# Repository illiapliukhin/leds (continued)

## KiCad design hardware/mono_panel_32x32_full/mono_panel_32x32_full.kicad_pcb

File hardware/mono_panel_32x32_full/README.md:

# mono_panel_32x32_full — edge-to-edge 32×32 panel for seamless tiling

A drop-in alternative to `mono_panel_32x32`: same two Hirose `FH12-40S-0.5SH` receptacles, same pinout and LED net mapping
(`Dn`, n = 32(r−1)+c; LED pad 2 = `ROW_rr_ANODE`, pad 1 = `COL_cc`), Type B FFC pin 1 → pin 1. There is no frame. LEDs fill the
whole front, so butted panels (6-stack, 3×2, 6×1) keep one continuous pixel grid.

## Geometry (for the stacking sim)

| | |
|---|---|
| Outline | **160.0 × 160.0 mm**, square, sharp corners, origin at the top-left corner of the front (KiCad +x right, +y down) |
| Pitch | **5.0 mm** in x and y |
| LED centres | x = 2.5 + 5.0·(c−1), y = 2.5 + 5.0·(r−1); the outermost LED centre is **2.5 mm (pitch/2)** from every edge |
| Across a seam | centre-to-centre = 5.0 mm, so the pitch is continuous; 3×2 = 480 × 320 mm, 96 × 64 LEDs; 6×1 = 960 × 160 mm |
| LED | NCD0603W1 (0603), long axis vertical, centred on the node; anode north |
| Thickness | 1.6 mm FR4, 4 layers; height with FFC ≈ 1.6 + 2.0 (FH12) mm; SMT standoffs on the back |
| Back parts | J_ROW centre (72.75, 80.0), J_COL centre (107.75, 80.0), both B.Cu, pin 1 at the left (front view), cable exits +y (south). U_ID (91.0, 76.9), C_ID (91.0, 74.3). Standoffs MH1–4 at (20, 16.9), (140, 16.9), (20, 141.9), (140, 141.9) |

## Choices

- **Pitch 5.0 mm (160 mm board).** Recommended over 4.0 and 3.0. 5.0 keeps the 0603 LEDs (good side visibility, the same LED and
  10 mA as today, so brightness per pixel is unchanged) and leaves a 1.7 mm-tall via band and about 4 mm channels per cell. That room is
  what lets the 64 FFC lines fan in on the back without blind vias. 4.0 mm (128 mm) also fits 0603 but the channels hold only about
  5 lines, so the fan-out would need 6 layers or HDI. 3.0 mm (96 mm) needs 0402 and laser vias. Cost per panel is about the same at
  5.0 and 4.0 (the LED count is fixed and the PCB is about 25 % smaller). At 3.0 HDI dominates. The pitch is close to the old
  panel's 5.2 mm, so content scales almost 1:1.
- **4 layers (JLC 1.6 mm, order 1 oz inner copper).** F.Cu: LEDs, 1.0 mm row bus on the anode line, cathode stubs to one
  0.2/0.45 mm via per LED (1.9 mm below the LED centre, so the bottom row's via keeps 0.35 mm to the edge). In1.Cu: the 32 column lines, straight under
  the vias. In2.Cu + B.Cu: FFC fan-out. Rows go straight up/down on B.Cu in the via channels (8 per channel) to a via on their
  own bus. Columns, ID and GND are maze-routed (`route_full.py`, A* on 0.125 mm grid, real clearance ≥ 0.10 mm).
- **Mounting: SMT M2 standoffs on the back, no front holes.** Four Ø4.2 mm SMD pads on B.Cu between via rows. Suggested parts:
  Würth WA-SMSI/WA-SMSN M2 (blind, flat-bottom) or similar no-hole SMT nuts. Check the exact MPN pad before ordering. PEM SMTSO and the
  LCSC SMTSO clones need a Ø3.7 board hole and are **not** compatible. Hand-solder them or consign them to JLC. The front stays solid LEDs.
- **LED interface standard v1** (`hardware/common/LED_INTERFACE_STANDARD.md`): J_ROW 33/38/40 = GND, 39 (`ID_PRESENT_N`) = GND,
  35/36 = ID_SDA/ID_SCL, 37 = ID_3V3; J_COL 33/38/40 = GND; 34 (and J_COL 34–37, 39) are NC. `U_ID` 24LC02BT-I/OT (0x50,
  pin 4 VCC, pin 5 WP = GND, no pull-ups) and `C_ID` 100 nF on ID_3V3. EEPROM record: class = full-bleed, pitch 5.0 mm,
  `row_path_mohm` = 148 (worst row, panel only), mapping identity.

## Current / IR drop (row = 32 × 10 mA = 0.32 A, `analyze_full.py` → `analysis.json`)

| | |
|---|---|
| Row feed | 0.30 mm × 1 oz on B.Cu, ≤ 80.7 mm (ROW_01) = 132 mΩ; jog sections 0.2 mm |
| Row bus | 1.0 mm × 1 oz F.Cu, fed at one point, worst bus drop 4.6 mV |
| Via | 1.75 mΩ (0.2 mm drill, 1.6 mm) |
| **Worst panel drop** | **47 mV at 20 °C, 55 mV at 60 °C** (target ≤ 100 mV) |
| Temperature rise | 0.3 mm at 0.32 A ≈ 4.6 °C (IPC-2221 external, conservative versus IPC-2152) |

## DRC / fab

- `kicad-cli pcb drc --severity-all`: **0 violations, 0 unconnected** (clearance 0.10, track ≥ 0.15, via 0.2/0.45, copper–edge 0.2).
- `./make_fab.sh` → `mono_panel_32x32_full_fab.zip` (Gerbers F/In1/In2/B, drill, BOM + CPL JLC format).
- **Assembly:** LEDs on top (1024 × C84265). The back has 2 × FH12 (C202114), U_ID (C2655410) and C_ID (C1525), so JLC needs **double-sided assembly**.
  A cheaper option: top-side assembly only, then hand-solder the 2 FFCs + 0402 + SOT-23 (and the standoffs).
- **Price (ESTIMATE, JLC/LCSC list prices, `fab/price_estimate.json`, priced BOM `fab/BOM_mono_panel_32x32_full_priced.csv`):**
  parts ≈ $8.5/board (1024 LEDs ≈ $7.0, 2 × FH12 ≈ $1.24, EEPROM $0.27); 4L 160×160 PCB with 1 oz inner ≈ $70 for 5;
  double-sided SMT setup ≈ $50 + 4 extended-part fees ≈ $12 → **≈ $38 per assembled panel at qty 5, ≈ $23 at qty 30**.
  Top-only assembly with the back parts hand-soldered saves about $25 per order.

## Renders (`renders/`)

`full_front_lit.png` (front, lit), `full_back.png` (back: copper of all layers + parts), `full_kicad_top.png` /
`full_kicad_bottom.png` (KiCad 3D), `full_tiled_3x2.png` (3×2 butted wall, red ticks = seams), `full_seam_closeup.png`, `full_sim_bg.png`.

## Regenerate

```
source ../tools/kicad10_env.sh
python3.11 gen_full.py          # base board + fixed.json
python3 route_full.py           # numpy/scipy maze router -> routes.json (~3 min)
python3.11 gen_full.py routes   # final .kicad_pcb
kicad-cli pcb drc --severity-all --format json -o drc.json mono_panel_32x32_full.kicad_pcb
python3 analyze_full.py && python3 render_full.py && ./make_fab.sh
```
Bring-up sim: `firmware/mono_split/sim/bringup/bringup.py --panel full`.

## Bring-up sim (`--panel full`)

`cable.py --panel full`: Type B gives J_ROW1→J_ROW and J_COL1→J_COL pin 1→1 with 0 net mismatches (Type A mirrors 1→40, 32 errors).
Nominal tests: I2C scan, all on, row walk, column walk, and checkerboard all **PASS** (32/32 rows and columns, 0 LED mismatches). Fault injection: F1 (Type A cable) and F2 (open COL_07) are **caught**.
See `firmware/mono_split/sim/bringup/bench_report_full.md` and `png/bringup_full_*.png`.

## LED Vf bin (order note)

NCD0603W1 (C84265) is sold unbinned on LCSC/JLC (2.6–3.6 V @ 5 mA). The main board's 4.24 V rail allows ≤ 3.38 V at 10 mA, which is about ≤ 3.2 V @ 5 mA. **Order Vf bin 2.8–3.0 V @ 5 mA (preferred) or 3.0–3.2 V; reject > 3.2 V**, one bin per panel. The bin is printed as `VF(V)` on the reel label, and NationStar has no part-number suffix for it. With JLC either consign labelled reels or accept unbinned parts and screen at bring-up. Details: `hardware/common/LED_INTERFACE_STANDARD.md` §5.1.

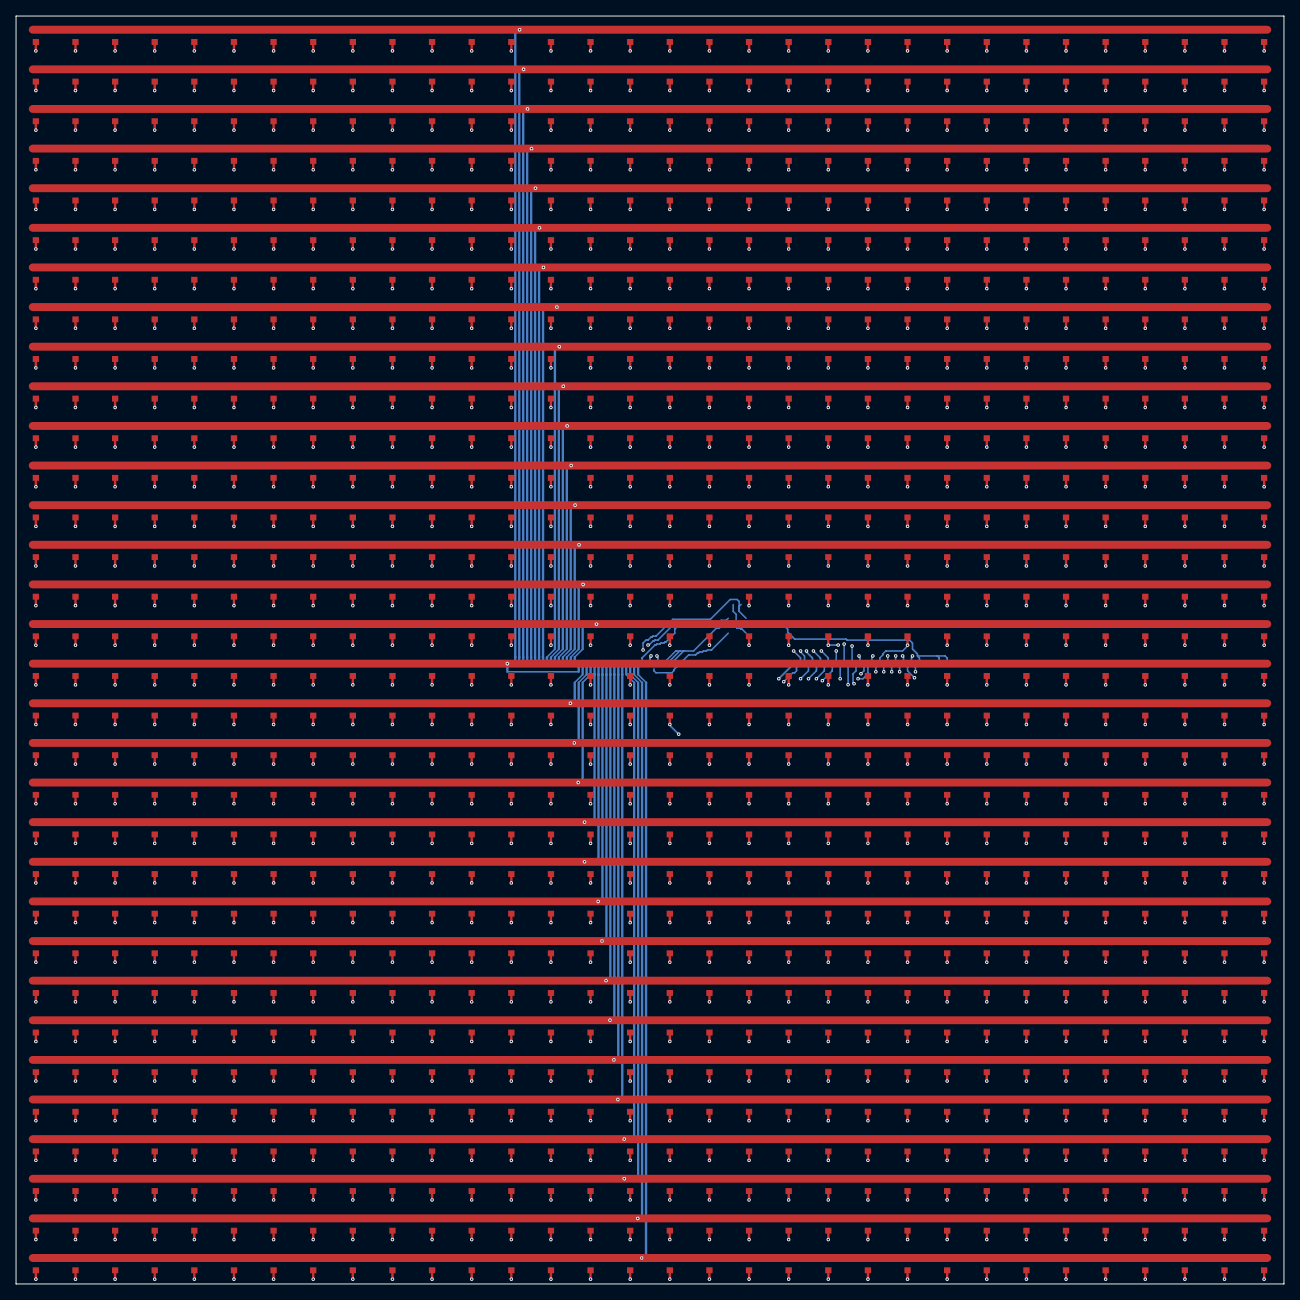
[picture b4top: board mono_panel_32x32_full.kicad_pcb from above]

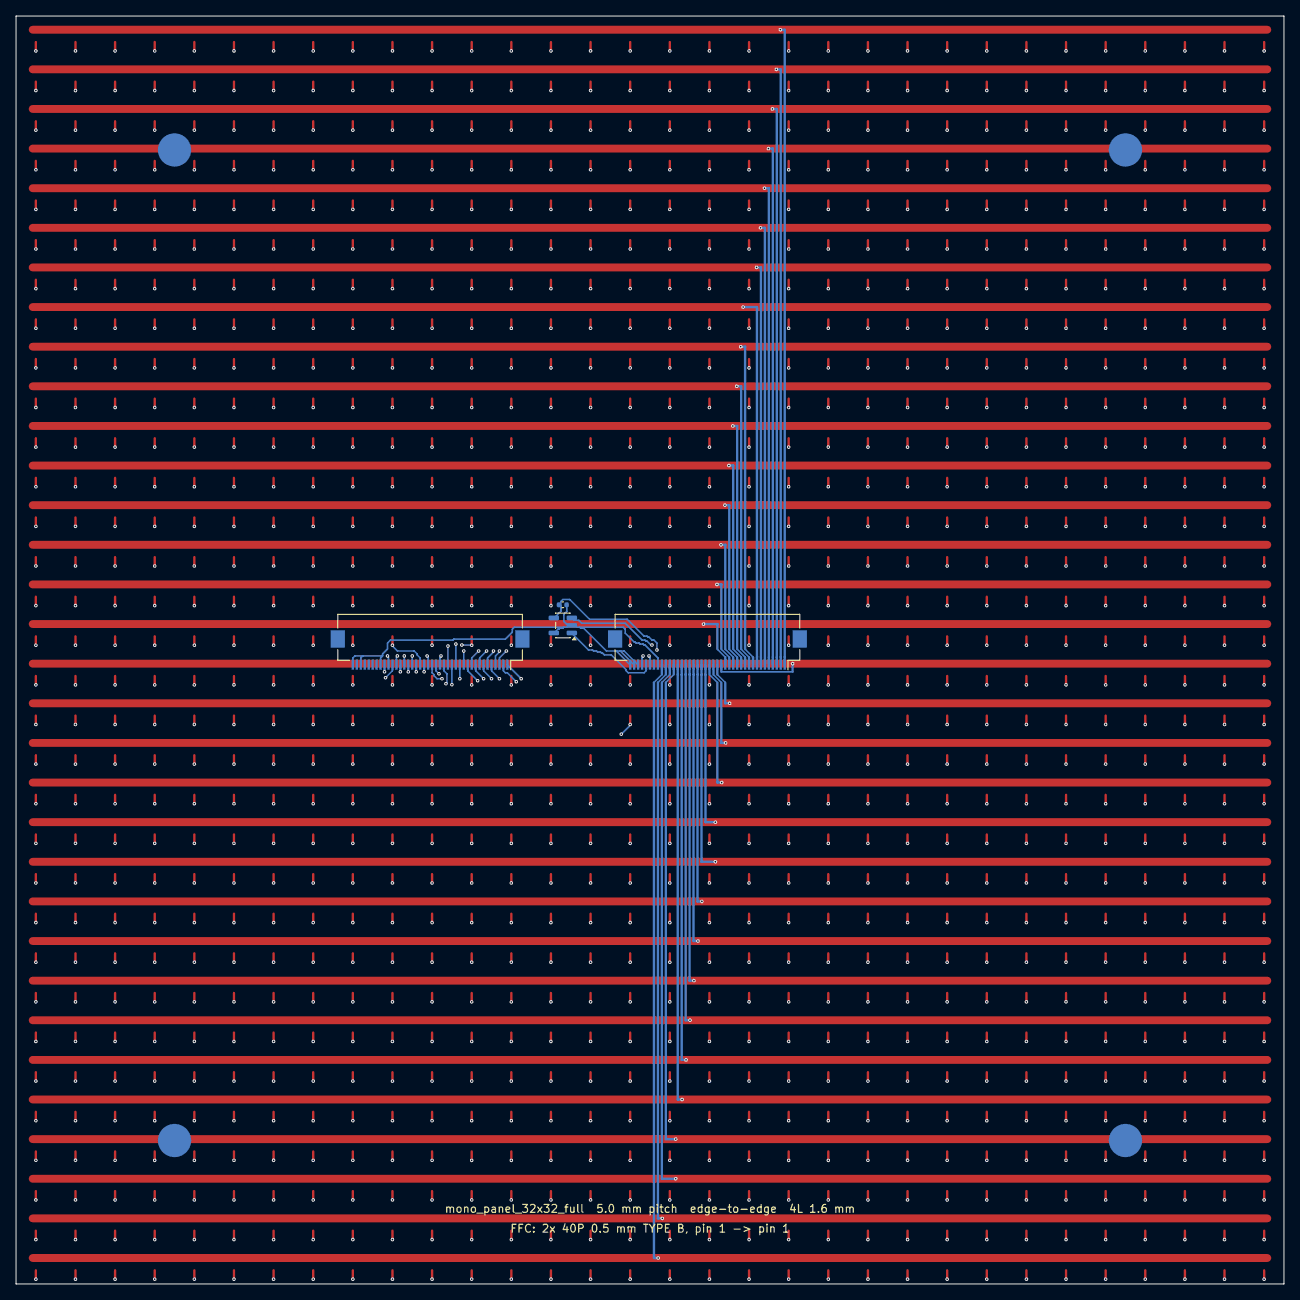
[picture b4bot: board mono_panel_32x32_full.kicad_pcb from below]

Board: 4 copper layers, 160.0 x 160.0 mm, 1032 parts (8 on the bottom side), 68 nets.

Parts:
C_ID: 100n; C_0402_1005Metric
D1, D2, D3, D4, D5, D6, D7, D8, D9, D10, D11, D12, D13, D14, D15, D16, D17, D18, D19, D20, D21, D22, D23, D24, D25, D26, D27, D28, D29, D30, D31, D32, D33, D34, D35, D36, D37, D38, D39, D40, D41, D42, D43, D44, D45, D46, D47, D48, D49, D50, D51, D52, D53, D54, D55, D56, D57, D58, D59, D60, D61, D62, D63, D64, D65, D66, D67, D68, D69, D70, D71, D72, D73, D74, D75, D76, D77, D78, D79, D80, D81, D82, D83, D84, D85, D86, D87, D88, D89, D90, D91, D92, D93, D94, D95, D96, D97, D98, D99, D100, D101, D102, D103, D104, D105, D106, D107, D108, D109, D110, D111, D112, D113, D114, D115, D116, D117, D118, D119, D120, D121, D122, D123, D124, D125, D126, D127, D128, D129, D130, D131, D132, D133, D134, D135, D136, D137, D138, D139, D140, D141, D142, D143, D144, D145, D146, D147, D148, D149, D150, D151, D152, D153, D154, D155, D156, D157, D158, D159, D160, D161, D162, D163, D164, D165, D166, D167, D168, D169, D170, D171, D172, D173, D174, D175, D176, D177, D178, D179, D180, D181, D182, D183, D184, D185, D186, D187, D188, D189, D190, D191, D192, D193, D194, D195, D196, D197, D198, D199, D200, D201, D202, D203, D204, D205, D206, D207, D208, D209, D210, D211, D212, D213, D214, D215, D216, D217, D218, D219, D220, D221, D222, D223, D224, D225, D226, D227, D228, D229, D230, D231, D232, D233, D234, D235, D236, D237, D238, D239, D240, D241, D242, D243, D244, D245, D246, D247, D248, D249, D250, D251, D252, D253, D254, D255, D256, D257, D258, D259, D260, D261, D262, D263, D264, D265, D266, D267, D268, D269, D270, D271, D272, D273, D274, D275, D276, D277, D278, D279, D280, D281, D282, D283, D284, D285, D286, D287, D288, D289, D290, D291, D292, D293, D294, D295, D296, D297, D298, D299, D300, D301, D302, D303, D304, D305, D306, D307, D308, D309, D310, D311, D312, D313, D314, D315, D316, D317, D318, D319, D320, D321, D322, D323, D324, D325, D326, D327, D328, D329, D330, D331, D332, D333, D334, D335, D336, D337, D338, D339, D340, D341, D342, D343, D344, D345, D346, D347, D348, D349, D350, D351, D352, D353, D354, D355, D356, D357, D358, D359, D360, D361, D362, D363, D364, D365, D366, D367, D368, D369, D370, D371, D372, D373, D374, D375, D376, D377, D378, D379, D380, D381, D382, D383, D384, D385, D386, D387, D388, D389, D390, D391, D392, D393, D394, D395, D396, D397, D398, D399, D400, D401, D402, D403, D404, D405, D406, D407, D408, D409, D410, D411, D412, D413, D414, D415, D416, D417, D418, D419, D420, D421, D422, D423, D424, D425, D426, D427, D428, D429, D430, D431, D432, D433, D434, D435, D436, D437, D438, D439, D440, D441, D442, D443, D444, D445, D446, D447, D448, D449, D450, D451, D452, D453, D454, D455, D456, D457, D458, D459, D460, D461, D462, D463, D464, D465, D466, D467, D468, D469, D470, D471, D472, D473, D474, D475, D476, D477, D478, D479, D480, D481, D482, D483, D484, D485, D486, D487, D488, D489, D490, D491, D492, D493, D494, D495, D496, D497, D498, D499, D500, D501, D502, D503, D504, D505, D506, D507, D508, D509, D510, D511, D512, D513, D514, D515, D516, D517, D518, D519, D520, D521, D522, D523, D524, D525, D526, D527, D528, D529, D530, D531, D532, D533, D534, D535, D536, D537, D538, D539, D540, D541, D542, D543, D544, D545, D546, D547, D548, D549, D550, D551, D552, D553, D554, D555, D556, D557, D558, D559, D560, D561, D562, D563, D564, D565, D566, D567, D568, D569, D570, D571, D572, D573, D574, D575, D576, D577, D578, D579, D580, D581, D582, D583, D584, D585, D586, D587, D588, D589, D590, D591, D592, D593, D594, D595, D596, D597, D598, D599, D600, D601, D602, D603, D604, D605, D606, D607, D608, D609, D610, D611, D612, D613, D614, D615, D616, D617, D618, D619, D620, D621, D622, D623, D624, D625, D626, D627, D628, D629, D630, D631, D632, D633, D634, D635, D636, D637, D638, D639, D640, D641, D642, D643, D644, D645, D646, D647, D648, D649, D650, D651, D652, D653, D654, D655, D656, D657, D658, D659, D660, D661, D662, D663, D664, D665, D666, D667, D668, D669, D670, D671, D672, D673, D674, D675, D676, D677, D678, D679, D680, D681, D682, D683, D684, D685, D686, D687, D688, D689, D690, D691, D692, D693, D694, D695, D696, D697, D698, D699, D700, D701, D702, D703, D704, D705, D706, D707, D708, D709, D710, D711, D712, D713, D714, D715, D716, D717, D718, D719, D720, D721, D722, D723, D724, D725, D726, D727, D728, D729, D730, D731, D732, D733, D734, D735, D736, D737, D738, D739, D740, D741, D742, D743, D744, D745, D746, D747, D748, D749, D750, D751, D752, D753, D754, D755, D756, D757, D758, D759, D760, D761, D762, D763, D764, D765, D766, D767, D768, D769, D770, D771, D772, D773, D774, D775, D776, D777, D778, D779, D780, D781, D782, D783, D784, D785, D786, D787, D788, D789, D790, D791, D792, D793, D794, D795, D796, D797, D798, D799, D800, D801, D802, D803, D804, D805, D806, D807, D808, D809, D810, D811, D812, D813, D814, D815, D816, D817, D818, D819, D820, D821, D822, D823, D824, D825, D826, D827, D828, D829, D830, D831, D832, D833, D834, D835, D836, D837, D838, D839, D840, D841, D842, D843, D844, D845, D846, D847, D848, D849, D850, D851, D852, D853, D854, D855, D856, D857, D858, D859, D860, D861, D862, D863, D864, D865, D866, D867, D868, D869, D870, D871, D872, D873, D874, D875, D876, D877, D878, D879, D880, D881, D882, D883, D884, D885, D886, D887, D888, D889, D890, D891, D892, D893, D894, D895, D896, D897, D898, D899, D900, D901, D902, D903, D904, D905, D906, D907, D908, D909, D910, D911, D912, D913, D914, D915, D916, D917, D918, D919, D920, D921, D922, D923, D924, D925, D926, D927, D928, D929, D930, D931, D932, D933, D934, D935, D936, D937, D938, D939, D940, D941, D942, D943, D944, D945, D946, D947, D948, D949, D950, D951, D952, D953, D954, D955, D956, D957, D958, D959, D960, D961, D962, D963, D964, D965, D966, D967, D968, D969, D970, D971, D972, D973, D974, D975, D976, D977, D978, D979, D980, D981, D982, D983, D984, D985, D986, D987, D988, D989, D990, D991, D992, D993, D994, D995, D996, D997, D998, D999, D1000, D1001, D1002, D1003, D1004, D1005, D1006, D1007, D1008, D1009, D1010, D1011, D1012, D1013, D1014, D1015, D1016, D1017, D1018, D1019, D1020, D1021, D1022, D1023, D1024: NCD0603W1
J_COL: FFC_40P_050_COL
J_ROW: FFC_40P_050_ROW
MH1, MH2, MH3, MH4: SMT_STANDOFF_M2; SMT_Standoff_M2_D4.2
U_ID: 24LC02BT-I/OT; SOT-23-5

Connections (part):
COL_01: D1.1 (K), D33.1 (K), D65.1 (K), D97.1 (K), D129.1 (K), D161.1 (K), D193.1 (K), D225.1 (K), D257.1 (K), D289.1 (K), D321.1 (K), D353.1 (K), D385.1 (K), D417.1 (K), D449.1 (K), D481.1 (K), D513.1 (K), D545.1 (K), D577.1 (K), D609.1 (K), D641.1 (K), D673.1 (K), D705.1 (K), D737.1 (K), D769.1 (K), D801.1 (K), D833.1 (K), D865.1 (K), D897.1 (K), D929.1 (K), D961.1 (K), D993.1 (K), J_COL.1
COL_02: D2.1 (K), D34.1 (K), D66.1 (K), D98.1 (K), D130.1 (K), D162.1 (K), D194.1 (K), D226.1 (K), D258.1 (K), D290.1 (K), D322.1 (K), D354.1 (K), D386.1 (K), D418.1 (K), D450.1 (K), D482.1 (K), D514.1 (K), D546.1 (K), D578.1 (K), D610.1 (K), D642.1 (K), D674.1 (K), D706.1 (K), D738.1 (K), D770.1 (K), D802.1 (K), D834.1 (K), D866.1 (K), D898.1 (K), D930.1 (K), D962.1 (K), D994.1 (K), J_COL.2
COL_03: D3.1 (K), D35.1 (K), D67.1 (K), D99.1 (K), D131.1 (K), D163.1 (K), D195.1 (K), D227.1 (K), D259.1 (K), D291.1 (K), D323.1 (K), D355.1 (K), D387.1 (K), D419.1 (K), D451.1 (K), D483.1 (K), D515.1 (K), D547.1 (K), D579.1 (K), D611.1 (K), D643.1 (K), D675.1 (K), D707.1 (K), D739.1 (K), D771.1 (K), D803.1 (K), D835.1 (K), D867.1 (K), D899.1 (K), D931.1 (K), D963.1 (K), D995.1 (K), J_COL.3
COL_04: D4.1 (K), D36.1 (K), D68.1 (K), D100.1 (K), D132.1 (K), D164.1 (K), D196.1 (K), D228.1 (K), D260.1 (K), D292.1 (K), D324.1 (K), D356.1 (K), D388.1 (K), D420.1 (K), D452.1 (K), D484.1 (K), D516.1 (K), D548.1 (K), D580.1 (K), D612.1 (K), D644.1 (K), D676.1 (K), D708.1 (K), D740.1 (K), D772.1 (K), D804.1 (K), D836.1 (K), D868.1 (K), D900.1 (K), D932.1 (K), D964.1 (K), D996.1 (K), J_COL.4
COL_05: D5.1 (K), D37.1 (K), D69.1 (K), D101.1 (K), D133.1 (K), D165.1 (K), D197.1 (K), D229.1 (K), D261.1 (K), D293.1 (K), D325.1 (K), D357.1 (K), D389.1 (K), D421.1 (K), D453.1 (K), D485.1 (K), D517.1 (K), D549.1 (K), D581.1 (K), D613.1 (K), D645.1 (K), D677.1 (K), D709.1 (K), D741.1 (K), D773.1 (K), D805.1 (K), D837.1 (K), D869.1 (K), D901.1 (K), D933.1 (K), D965.1 (K), D997.1 (K), J_COL.5
COL_06: D6.1 (K), D38.1 (K), D70.1 (K), D102.1 (K), D134.1 (K), D166.1 (K), D198.1 (K), D230.1 (K), D262.1 (K), D294.1 (K), D326.1 (K), D358.1 (K), D390.1 (K), D422.1 (K), D454.1 (K), D486.1 (K), D518.1 (K), D550.1 (K), D582.1 (K), D614.1 (K), D646.1 (K), D678.1 (K), D710.1 (K), D742.1 (K), D774.1 (K), D806.1 (K), D838.1 (K), D870.1 (K), D902.1 (K), D934.1 (K), D966.1 (K), D998.1 (K), J_COL.6
COL_07: D7.1 (K), D39.1 (K), D71.1 (K), D103.1 (K), D135.1 (K), D167.1 (K), D199.1 (K), D231.1 (K), D263.1 (K), D295.1 (K), D327.1 (K), D359.1 (K), D391.1 (K), D423.1 (K), D455.1 (K), D487.1 (K), D519.1 (K), D551.1 (K), D583.1 (K), D615.1 (K), D647.1 (K), D679.1 (K), D711.1 (K), D743.1 (K), D775.1 (K), D807.1 (K), D839.1 (K), D871.1 (K), D903.1 (K), D935.1 (K), D967.1 (K), D999.1 (K), J_COL.7
COL_08: D8.1 (K), D40.1 (K), D72.1 (K), D104.1 (K), D136.1 (K), D168.1 (K), D200.1 (K), D232.1 (K), D264.1 (K), D296.1 (K), D328.1 (K), D360.1 (K), D392.1 (K), D424.1 (K), D456.1 (K), D488.1 (K), D520.1 (K), D552.1 (K), D584.1 (K), D616.1 (K), D648.1 (K), D680.1 (K), D712.1 (K), D744.1 (K), D776.1 (K), D808.1 (K), D840.1 (K), D872.1 (K), D904.1 (K), D936.1 (K), D968.1 (K), D1000.1 (K), J_COL.8
COL_09: D9.1 (K), D41.1 (K), D73.1 (K), D105.1 (K), D137.1 (K), D169.1 (K), D201.1 (K), D233.1 (K), D265.1 (K), D297.1 (K), D329.1 (K), D361.1 (K), D393.1 (K), D425.1 (K), D457.1 (K), D489.1 (K), D521.1 (K), D553.1 (K), D585.1 (K), D617.1 (K), D649.1 (K), D681.1 (K), D713.1 (K), D745.1 (K), D777.1 (K), D809.1 (K), D841.1 (K), D873.1 (K), D905.1 (K), D937.1 (K), D969.1 (K), D1001.1 (K), J_COL.9
COL_10: D10.1 (K), D42.1 (K), D74.1 (K), D106.1 (K), D138.1 (K), D170.1 (K), D202.1 (K), D234.1 (K), D266.1 (K), D298.1 (K), D330.1 (K), D362.1 (K), D394.1 (K), D426.1 (K), D458.1 (K), D490.1 (K), D522.1 (K), D554.1 (K), D586.1 (K), D618.1 (K), D650.1 (K), D682.1 (K), D714.1 (K), D746.1 (K), D778.1 (K), D810.1 (K), D842.1 (K), D874.1 (K), D906.1 (K), D938.1 (K), D970.1 (K), D1002.1 (K), J_COL.10
COL_11: D11.1 (K), D43.1 (K), D75.1 (K), D107.1 (K), D139.1 (K), D171.1 (K), D203.1 (K), D235.1 (K), D267.1 (K), D299.1 (K), D331.1 (K), D363.1 (K), D395.1 (K), D427.1 (K), D459.1 (K), D491.1 (K), D523.1 (K), D555.1 (K), D587.1 (K), D619.1 (K), D651.1 (K), D683.1 (K), D715.1 (K), D747.1 (K), D779.1 (K), D811.1 (K), D843.1 (K), D875.1 (K), D907.1 (K), D939.1 (K), D971.1 (K), D1003.1 (K), J_COL.11
COL_12: D12.1 (K), D44.1 (K), D76.1 (K), D108.1 (K), D140.1 (K), D172.1 (K), D204.1 (K), D236.1 (K), D268.1 (K), D300.1 (K), D332.1 (K), D364.1 (K), D396.1 (K), D428.1 (K), D460.1 (K), D492.1 (K), D524.1 (K), D556.1 (K), D588.1 (K), D620.1 (K), D652.1 (K), D684.1 (K), D716.1 (K), D748.1 (K), D780.1 (K), D812.1 (K), D844.1 (K), D876.1 (K), D908.1 (K), D940.1 (K), D972.1 (K), D1004.1 (K), J_COL.12
COL_13: D13.1 (K), D45.1 (K), D77.1 (K), D109.1 (K), D141.1 (K), D173.1 (K), D205.1 (K), D237.1 (K), D269.1 (K), D301.1 (K), D333.1 (K), D365.1 (K), D397.1 (K), D429.1 (K), D461.1 (K), D493.1 (K), D525.1 (K), D557.1 (K), D589.1 (K), D621.1 (K), D653.1 (K), D685.1 (K), D717.1 (K), D749.1 (K), D781.1 (K), D813.1 (K), D845.1 (K), D877.1 (K), D909.1 (K), D941.1 (K), D973.1 (K), D1005.1 (K), J_COL.13
COL_14: D14.1 (K), D46.1 (K), D78.1 (K), D110.1 (K), D142.1 (K), D174.1 (K), D206.1 (K), D238.1 (K), D270.1 (K), D302.1 (K), D334.1 (K), D366.1 (K), D398.1 (K), D430.1 (K), D462.1 (K), D494.1 (K), D526.1 (K), D558.1 (K), D590.1 (K), D622.1 (K), D654.1 (K), D686.1 (K), D718.1 (K), D750.1 (K), D782.1 (K), D814.1 (K), D846.1 (K), D878.1 (K), D910.1 (K), D942.1 (K), D974.1 (K), D1006.1 (K), J_COL.14
COL_15: D15.1 (K), D47.1 (K), D79.1 (K), D111.1 (K), D143.1 (K), D175.1 (K), D207.1 (K), D239.1 (K), D271.1 (K), D303.1 (K), D335.1 (K), D367.1 (K), D399.1 (K), D431.1 (K), D463.1 (K), D495.1 (K), D527.1 (K), D559.1 (K), D591.1 (K), D623.1 (K), D655.1 (K), D687.1 (K), D719.1 (K), D751.1 (K), D783.1 (K), D815.1 (K), D847.1 (K), D879.1 (K), D911.1 (K), D943.1 (K), D975.1 (K), D1007.1 (K), J_COL.15
COL_16: D16.1 (K), D48.1 (K), D80.1 (K), D112.1 (K), D144.1 (K), D176.1 (K), D208.1 (K), D240.1 (K), D272.1 (K), D304.1 (K), D336.1 (K), D368.1 (K), D400.1 (K), D432.1 (K), D464.1 (K), D496.1 (K), D528.1 (K), D560.1 (K), D592.1 (K), D624.1 (K), D656.1 (K), D688.1 (K), D720.1 (K), D752.1 (K), D784.1 (K), D816.1 (K), D848.1 (K), D880.1 (K), D912.1 (K), D944.1 (K), D976.1 (K), D1008.1 (K), J_COL.16
COL_17: D17.1 (K), D49.1 (K), D81.1 (K), D113.1 (K), D145.1 (K), D177.1 (K), D209.1 (K), D241.1 (K), D273.1 (K), D305.1 (K), D337.1 (K), D369.1 (K), D401.1 (K), D433.1 (K), D465.1 (K), D497.1 (K), D529.1 (K), D561.1 (K), D593.1 (K), D625.1 (K), D657.1 (K), D689.1 (K), D721.1 (K), D753.1 (K), D785.1 (K), D817.1 (K), D849.1 (K), D881.1 (K), D913.1 (K), D945.1 (K), D977.1 (K), D1009.1 (K), J_COL.17
COL_18: D18.1 (K), D50.1 (K), D82.1 (K), D114.1 (K), D146.1 (K), D178.1 (K), D210.1 (K), D242.1 (K), D274.1 (K), D306.1 (K), D338.1 (K), D370.1 (K), D402.1 (K), D434.1 (K), D466.1 (K), D498.1 (K), D530.1 (K), D562.1 (K), D594.1 (K), D626.1 (K), D658.1 (K), D690.1 (K), D722.1 (K), D754.1 (K), D786.1 (K), D818.1 (K), D850.1 (K), D882.1 (K), D914.1 (K), D946.1 (K), D978.1 (K), D1010.1 (K), J_COL.18
COL_19: D19.1 (K), D51.1 (K), D83.1 (K), D115.1 (K), D147.1 (K), D179.1 (K), D211.1 (K), D243.1 (K), D275.1 (K), D307.1 (K), D339.1 (K), D371.1 (K), D403.1 (K), D435.1 (K), D467.1 (K), D499.1 (K), D531.1 (K), D563.1 (K), D595.1 (K), D627.1 (K), D659.1 (K), D691.1 (K), D723.1 (K), D755.1 (K), D787.1 (K), D819.1 (K), D851.1 (K), D883.1 (K), D915.1 (K), D947.1 (K), D979.1 (K), D1011.1 (K), J_COL.19
COL_20: D20.1 (K), D52.1 (K), D84.1 (K), D116.1 (K), D148.1 (K), D180.1 (K), D212.1 (K), D244.1 (K), D276.1 (K), D308.1 (K), D340.1 (K), D372.1 (K), D404.1 (K), D436.1 (K), D468.1 (K), D500.1 (K), D532.1 (K), D564.1 (K), D596.1 (K), D628.1 (K), D660.1 (K), D692.1 (K), D724.1 (K), D756.1 (K), D788.1 (K), D820.1 (K), D852.1 (K), D884.1 (K), D916.1 (K), D948.1 (K), D980.1 (K), D1012.1 (K), J_COL.20
COL_21: D21.1 (K), D53.1 (K), D85.1 (K), D117.1 (K), D149.1 (K), D181.1 (K), D213.1 (K), D245.1 (K), D277.1 (K), D309.1 (K), D341.1 (K), D373.1 (K), D405.1 (K), D437.1 (K), D469.1 (K), D501.1 (K), D533.1 (K), D565.1 (K), D597.1 (K), D629.1 (K), D661.1 (K), D693.1 (K), D725.1 (K), D757.1 (K), D789.1 (K), D821.1 (K), D853.1 (K), D885.1 (K), D917.1 (K), D949.1 (K), D981.1 (K), D1013.1 (K), J_COL.21
COL_22: D22.1 (K), D54.1 (K), D86.1 (K), D118.1 (K), D150.1 (K), D182.1 (K), D214.1 (K), D246.1 (K), D278.1 (K), D310.1 (K), D342.1 (K), D374.1 (K), D406.1 (K), D438.1 (K), D470.1 (K), D502.1 (K), D534.1 (K), D566.1 (K), D598.1 (K), D630.1 (K), D662.1 (K), D694.1 (K), D726.1 (K), D758.1 (K), D790.1 (K), D822.1 (K), D854.1 (K), D886.1 (K), D918.1 (K), D950.1 (K), D982.1 (K), D1014.1 (K), J_COL.22
COL_23: D23.1 (K), D55.1 (K), D87.1 (K), D119.1 (K), D151.1 (K), D183.1 (K), D215.1 (K), D247.1 (K), D279.1 (K), D311.1 (K), D343.1 (K), D375.1 (K), D407.1 (K), D439.1 (K), D471.1 (K), D503.1 (K), D535.1 (K), D567.1 (K), D599.1 (K), D631.1 (K), D663.1 (K), D695.1 (K), D727.1 (K), D759.1 (K), D791.1 (K), D823.1 (K), D855.1 (K), D887.1 (K), D919.1 (K), D951.1 (K), D983.1 (K), D1015.1 (K), J_COL.23
COL_24: D24.1 (K), D56.1 (K), D88.1 (K), D120.1 (K), D152.1 (K), D184.1 (K), D216.1 (K), D248.1 (K), D280.1 (K), D312.1 (K), D344.1 (K), D376.1 (K), D408.1 (K), D440.1 (K), D472.1 (K), D504.1 (K), D536.1 (K), D568.1 (K), D600.1 (K), D632.1 (K), D664.1 (K), D696.1 (K), D728.1 (K), D760.1 (K), D792.1 (K), D824.1 (K), D856.1 (K), D888.1 (K), D920.1 (K), D952.1 (K), D984.1 (K), D1016.1 (K), J_COL.24
COL_25: D25.1 (K), D57.1 (K), D89.1 (K), D121.1 (K), D153.1 (K), D185.1 (K), D217.1 (K), D249.1 (K), D281.1 (K), D313.1 (K), D345.1 (K), D377.1 (K), D409.1 (K), D441.1 (K), D473.1 (K), D505.1 (K), D537.1 (K), D569.1 (K), D601.1 (K), D633.1 (K), D665.1 (K), D697.1 (K), D729.1 (K), D761.1 (K), D793.1 (K), D825.1 (K), D857.1 (K), D889.1 (K), D921.1 (K), D953.1 (K), D985.1 (K), D1017.1 (K), J_COL.25
COL_26: D26.1 (K), D58.1 (K), D90.1 (K), D122.1 (K), D154.1 (K), D186.1 (K), D218.1 (K), D250.1 (K), D282.1 (K), D314.1 (K), D346.1 (K), D378.1 (K), D410.1 (K), D442.1 (K), D474.1 (K), D506.1 (K), D538.1 (K), D570.1 (K), D602.1 (K), D634.1 (K), D666.1 (K), D698.1 (K), D730.1 (K), D762.1 (K), D794.1 (K), D826.1 (K), D858.1 (K), D890.1 (K), D922.1 (K), D954.1 (K), D986.1 (K), D1018.1 (K), J_COL.26
COL_27: D27.1 (K), D59.1 (K), D91.1 (K), D123.1 (K), D155.1 (K), D187.1 (K), D219.1 (K), D251.1 (K), D283.1 (K), D315.1 (K), D347.1 (K), D379.1 (K), D411.1 (K), D443.1 (K), D475.1 (K), D507.1 (K), D539.1 (K), D571.1 (K), D603.1 (K), D635.1 (K), D667.1 (K), D699.1 (K), D731.1 (K), D763.1 (K), D795.1 (K), D827.1 (K), D859.1 (K), D891.1 (K), D923.1 (K), D955.1 (K), D987.1 (K), D1019.1 (K), J_COL.27
COL_28: D28.1 (K), D60.1 (K), D92.1 (K), D124.1 (K), D156.1 (K), D188.1 (K), D220.1 (K), D252.1 (K), D284.1 (K), D316.1 (K), D348.1 (K), D380.1 (K), D412.1 (K), D444.1 (K), D476.1 (K), D508.1 (K), D540.1 (K), D572.1 (K), D604.1 (K), D636.1 (K), D668.1 (K), D700.1 (K), D732.1 (K), D764.1 (K), D796.1 (K), D828.1 (K), D860.1 (K), D892.1 (K), D924.1 (K), D956.1 (K), D988.1 (K), D1020.1 (K), J_COL.28
COL_29: D29.1 (K), D61.1 (K), D93.1 (K), D125.1 (K), D157.1 (K), D189.1 (K), D221.1 (K), D253.1 (K), D285.1 (K), D317.1 (K), D349.1 (K), D381.1 (K), D413.1 (K), D445.1 (K), D477.1 (K), D509.1 (K), D541.1 (K), D573.1 (K), D605.1 (K), D637.1 (K), D669.1 (K), D701.1 (K), D733.1 (K), D765.1 (K), D797.1 (K), D829.1 (K), D861.1 (K), D893.1 (K), D925.1 (K), D957.1 (K), D989.1 (K), D1021.1 (K), J_COL.29
COL_30: D30.1 (K), D62.1 (K), D94.1 (K), D126.1 (K), D158.1 (K), D190.1 (K), D222.1 (K), D254.1 (K), D286.1 (K), D318.1 (K), D350.1 (K), D382.1 (K), D414.1 (K), D446.1 (K), D478.1 (K), D510.1 (K), D542.1 (K), D574.1 (K), D606.1 (K), D638.1 (K), D670.1 (K), D702.1 (K), D734.1 (K), D766.1 (K), D798.1 (K), D830.1 (K), D862.1 (K), D894.1 (K), D926.1 (K), D958.1 (K), D990.1 (K), D1022.1 (K), J_COL.30
COL_31: D31.1 (K), D63.1 (K), D95.1 (K), D127.1 (K), D159.1 (K), D191.1 (K), D223.1 (K), D255.1 (K), D287.1 (K), D319.1 (K), D351.1 (K), D383.1 (K), D415.1 (K), D447.1 (K), D479.1 (K), D511.1 (K), D543.1 (K), D575.1 (K), D607.1 (K), D639.1 (K), D671.1 (K), D703.1 (K), D735.1 (K), D767.1 (K), D799.1 (K), D831.1 (K), D863.1 (K), D895.1 (K), D927.1 (K), D959.1 (K), D991.1 (K), D1023.1 (K), J_COL.31
COL_32: D32.1 (K), D64.1 (K), D96.1 (K), D128.1 (K), D160.1 (K), D192.1 (K), D224.1 (K), D256.1 (K), D288.1 (K), D320.1 (K), D352.1 (K), D384.1 (K), D416.1 (K), D448.1 (K), D480.1 (K), D512.1 (K), D544.1 (K), D576.1 (K), D608.1 (K), D640.1 (K), D672.1 (K), D704.1 (K), D736.1 (K), D768.1 (K), D800.1 (K), D832.1 (K), D864.1 (K), D896.1 (K), D928.1 (K), D960.1 (K), D992.1 (K), D1024.1 (K), J_COL.32
GND: C_ID.2, J_COL.33, J_COL.38, J_COL.40, J_ROW.33, J_ROW.38, J_ROW.39, J_ROW.40, U_ID.2, U_ID.5
ID_3V3: C_ID.1, J_ROW.37, U_ID.4
ID_SCL: J_ROW.36, U_ID.1
ID_SDA: J_ROW.35, U_ID.3
ROW_01_ANODE: D1.2 (A), D2.2 (A), D3.2 (A), D4.2 (A), D5.2 (A), D6.2 (A), D7.2 (A), D8.2 (A), D9.2 (A), D10.2 (A), D11.2 (A), D12.2 (A), D13.2 (A), D14.2 (A), D15.2 (A), D16.2 (A), D17.2 (A), D18.2 (A), D19.2 (A), D20.2 (A), D21.2 (A), D22.2 (A), D23.2 (A), D24.2 (A), D25.2 (A), D26.2 (A), D27.2 (A), D28.2 (A), D29.2 (A), D30.2 (A), D31.2 (A), D32.2 (A), J_ROW.1
ROW_02_ANODE: D33.2 (A), D34.2 (A), D35.2 (A), D36.2 (A), D37.2 (A), D38.2 (A), D39.2 (A), D40.2 (A), D41.2 (A), D42.2 (A), D43.2 (A), D44.2 (A), D45.2 (A), D46.2 (A), D47.2 (A), D48.2 (A), D49.2 (A), D50.2 (A), D51.2 (A), D52.2 (A), D53.2 (A), D54.2 (A), D55.2 (A), D56.2 (A), D57.2 (A), D58.2 (A), D59.2 (A), D60.2 (A), D61.2 (A), D62.2 (A), D63.2 (A), D64.2 (A), J_ROW.2
ROW_03_ANODE: D65.2 (A), D66.2 (A), D67.2 (A), D68.2 (A), D69.2 (A), D70.2 (A), D71.2 (A), D72.2 (A), D73.2 (A), D74.2 (A), D75.2 (A), D76.2 (A), D77.2 (A), D78.2 (A), D79.2 (A), D80.2 (A), D81.2 (A), D82.2 (A), D83.2 (A), D84.2 (A), D85.2 (A), D86.2 (A), D87.2 (A), D88.2 (A), D89.2 (A), D90.2 (A), D91.2 (A), D92.2 (A), D93.2 (A), D94.2 (A), D95.2 (A), D96.2 (A), J_ROW.3
ROW_04_ANODE: D97.2 (A), D98.2 (A), D99.2 (A), D100.2 (A), D101.2 (A), D102.2 (A), D103.2 (A), D104.2 (A), D105.2 (A), D106.2 (A), D107.2 (A), D108.2 (A), D109.2 (A), D110.2 (A), D111.2 (A), D112.2 (A), D113.2 (A), D114.2 (A), D115.2 (A), D116.2 (A), D117.2 (A), D118.2 (A), D119.2 (A), D120.2 (A), D121.2 (A), D122.2 (A), D123.2 (A), D124.2 (A), D125.2 (A), D126.2 (A), D127.2 (A), D128.2 (A), J_ROW.4
ROW_05_ANODE: D129.2 (A), D130.2 (A), D131.2 (A), D132.2 (A), D133.2 (A), D134.2 (A), D135.2 (A), D136.2 (A), D137.2 (A), D138.2 (A), D139.2 (A), D140.2 (A), D141.2 (A), D142.2 (A), D143.2 (A), D144.2 (A), D145.2 (A), D146.2 (A), D147.2 (A), D148.2 (A), D149.2 (A), D150.2 (A), D151.2 (A), D152.2 (A), D153.2 (A), D154.2 (A), D155.2 (A), D156.2 (A), D157.2 (A), D158.2 (A), D159.2 (A), D160.2 (A), J_ROW.5
ROW_06_ANODE: D161.2 (A), D162.2 (A), D163.2 (A), D164.2 (A), D165.2 (A), D166.2 (A), D167.2 (A), D168.2 (A), D169.2 (A), D170.2 (A), D171.2 (A), D172.2 (A), D173.2 (A), D174.2 (A), D175.2 (A), D176.2 (A), D177.2 (A), D178.2 (A), D179.2 (A), D180.2 (A), D181.2 (A), D182.2 (A), D183.2 (A), D184.2 (A), D185.2 (A), D186.2 (A), D187.2 (A), D188.2 (A), D189.2 (A), D190.2 (A), D191.2 (A), D192.2 (A), J_ROW.6
ROW_07_ANODE: D193.2 (A), D194.2 (A), D195.2 (A), D196.2 (A), D197.2 (A), D198.2 (A), D199.2 (A), D200.2 (A), D201.2 (A), D202.2 (A), D203.2 (A), D204.2 (A), D205.2 (A), D206.2 (A), D207.2 (A), D208.2 (A), D209.2 (A), D210.2 (A), D211.2 (A), D212.2 (A), D213.2 (A), D214.2 (A), D215.2 (A), D216.2 (A), D217.2 (A), D218.2 (A), D219.2 (A), D220.2 (A), D221.2 (A), D222.2 (A), D223.2 (A), D224.2 (A), J_ROW.7
ROW_08_ANODE: D225.2 (A), D226.2 (A), D227.2 (A), D228.2 (A), D229.2 (A), D230.2 (A), D231.2 (A), D232.2 (A), D233.2 (A), D234.2 (A), D235.2 (A), D236.2 (A), D237.2 (A), D238.2 (A), D239.2 (A), D240.2 (A), D241.2 (A), D242.2 (A), D243.2 (A), D244.2 (A), D245.2 (A), D246.2 (A), D247.2 (A), D248.2 (A), D249.2 (A), D250.2 (A), D251.2 (A), D252.2 (A), D253.2 (A), D254.2 (A), D255.2 (A), D256.2 (A), J_ROW.8
ROW_09_ANODE: D257.2 (A), D258.2 (A), D259.2 (A), D260.2 (A), D261.2 (A), D262.2 (A), D263.2 (A), D264.2 (A), D265.2 (A), D266.2 (A), D267.2 (A), D268.2 (A), D269.2 (A), D270.2 (A), D271.2 (A), D272.2 (A), D273.2 (A), D274.2 (A), D275.2 (A), D276.2 (A), D277.2 (A), D278.2 (A), D279.2 (A), D280.2 (A), D281.2 (A), D282.2 (A), D283.2 (A), D284.2 (A), D285.2 (A), D286.2 (A), D287.2 (A), D288.2 (A), J_ROW.9
ROW_10_ANODE: D289.2 (A), D290.2 (A), D291.2 (A), D292.2 (A), D293.2 (A), D294.2 (A), D295.2 (A), D296.2 (A), D297.2 (A), D298.2 (A), D299.2 (A), D300.2 (A), D301.2 (A), D302.2 (A), D303.2 (A), D304.2 (A), D305.2 (A), D306.2 (A), D307.2 (A), D308.2 (A), D309.2 (A), D310.2 (A), D311.2 (A), D312.2 (A), D313.2 (A), D314.2 (A), D315.2 (A), D316.2 (A), D317.2 (A), D318.2 (A), D319.2 (A), D320.2 (A), J_ROW.10
ROW_11_ANODE: D321.2 (A), D322.2 (A), D323.2 (A), D324.2 (A), D325.2 (A), D326.2 (A), D327.2 (A), D328.2 (A), D329.2 (A), D330.2 (A), D331.2 (A), D332.2 (A), D333.2 (A), D334.2 (A), D335.2 (A), D336.2 (A), D337.2 (A), D338.2 (A), D339.2 (A), D340.2 (A), D341.2 (A), D342.2 (A), D343.2 (A), D344.2 (A), D345.2 (A), D346.2 (A), D347.2 (A), D348.2 (A), D349.2 (A), D350.2 (A), D351.2 (A), D352.2 (A), J_ROW.11
ROW_12_ANODE: D353.2 (A), D354.2 (A), D355.2 (A), D356.2 (A), D357.2 (A), D358.2 (A), D359.2 (A), D360.2 (A), D361.2 (A), D362.2 (A), D363.2 (A), D364.2 (A), D365.2 (A), D366.2 (A), D367.2 (A), D368.2 (A), D369.2 (A), D370.2 (A), D371.2 (A), D372.2 (A), D373.2 (A), D374.2 (A), D375.2 (A), D376.2 (A), D377.2 (A), D378.2 (A), D379.2 (A), D380.2 (A), D381.2 (A), D382.2 (A), D383.2 (A), D384.2 (A), J_ROW.12
ROW_13_ANODE: D385.2 (A), D386.2 (A), D387.2 (A), D388.2 (A), D389.2 (A), D390.2 (A), D391.2 (A), D392.2 (A), D393.2 (A), D394.2 (A), D395.2 (A), D396.2 (A), D397.2 (A), D398.2 (A), D399.2 (A), D400.2 (A), D401.2 (A), D402.2 (A), D403.2 (A), D404.2 (A), D405.2 (A), D406.2 (A), D407.2 (A), D408.2 (A), D409.2 (A), D410.2 (A), D411.2 (A), D412.2 (A), D413.2 (A), D414.2 (A), D415.2 (A), D416.2 (A), J_ROW.13
ROW_14_ANODE: D417.2 (A), D418.2 (A), D419.2 (A), D420.2 (A), D421.2 (A), D422.2 (A), D423.2 (A), D424.2 (A), D425.2 (A), D426.2 (A), D427.2 (A), D428.2 (A), D429.2 (A), D430.2 (A), D431.2 (A), D432.2 (A), D433.2 (A), D434.2 (A), D435.2 (A), D436.2 (A), D437.2 (A), D438.2 (A), D439.2 (A), D440.2 (A), D441.2 (A), D442.2 (A), D443.2 (A), D444.2 (A), D445.2 (A), D446.2 (A), D447.2 (A), D448.2 (A), J_ROW.14
ROW_15_ANODE: D449.2 (A), D450.2 (A), D451.2 (A), D452.2 (A), D453.2 (A), D454.2 (A), D455.2 (A), D456.2 (A), D457.2 (A), D458.2 (A), D459.2 (A), D460.2 (A), D461.2 (A), D462.2 (A), D463.2 (A), D464.2 (A), D465.2 (A), D466.2 (A), D467.2 (A), D468.2 (A), D469.2 (A), D470.2 (A), D471.2 (A), D472.2 (A), D473.2 (A), D474.2 (A), D475.2 (A), D476.2 (A), D477.2 (A), D478.2 (A), D479.2 (A), D480.2 (A), J_ROW.15
ROW_16_ANODE: D481.2 (A), D482.2 (A), D483.2 (A), D484.2 (A), D485.2 (A), D486.2 (A), D487.2 (A), D488.2 (A), D489.2 (A), D490.2 (A), D491.2 (A), D492.2 (A), D493.2 (A), D494.2 (A), D495.2 (A), D496.2 (A), D497.2 (A), D498.2 (A), D499.2 (A), D500.2 (A), D501.2 (A), D502.2 (A), D503.2 (A), D504.2 (A), D505.2 (A), D506.2 (A), D507.2 (A), D508.2 (A), D509.2 (A), D510.2 (A), D511.2 (A), D512.2 (A), J_ROW.16
ROW_17_ANODE: D513.2 (A), D514.2 (A), D515.2 (A), D516.2 (A), D517.2 (A), D518.2 (A), D519.2 (A), D520.2 (A), D521.2 (A), D522.2 (A), D523.2 (A), D524.2 (A), D525.2 (A), D526.2 (A), D527.2 (A), D528.2 (A), D529.2 (A), D530.2 (A), D531.2 (A), D532.2 (A), D533.2 (A), D534.2 (A), D535.2 (A), D536.2 (A), D537.2 (A), D538.2 (A), D539.2 (A), D540.2 (A), D541.2 (A), D542.2 (A), D543.2 (A), D544.2 (A), J_ROW.17
ROW_18_ANODE: D545.2 (A), D546.2 (A), D547.2 (A), D548.2 (A), D549.2 (A), D550.2 (A), D551.2 (A), D552.2 (A), D553.2 (A), D554.2 (A), D555.2 (A), D556.2 (A), D557.2 (A), D558.2 (A), D559.2 (A), D560.2 (A), D561.2 (A), D562.2 (A), D563.2 (A), D564.2 (A), D565.2 (A), D566.2 (A), D567.2 (A), D568.2 (A), D569.2 (A), D570.2 (A), D571.2 (A), D572.2 (A), D573.2 (A), D574.2 (A), D575.2 (A), D576.2 (A), J_ROW.18
ROW_19_ANODE: D577.2 (A), D578.2 (A), D579.2 (A), D580.2 (A), D581.2 (A), D582.2 (A), D583.2 (A), D584.2 (A), D585.2 (A), D586.2 (A), D587.2 (A), D588.2 (A), D589.2 (A), D590.2 (A), D591.2 (A), D592.2 (A), D593.2 (A), D594.2 (A), D595.2 (A), D596.2 (A), D597.2 (A), D598.2 (A), D599.2 (A), D600.2 (A), D601.2 (A), D602.2 (A), D603.2 (A), D604.2 (A), D605.2 (A), D606.2 (A), D607.2 (A), D608.2 (A), J_ROW.19
ROW_20_ANODE: D609.2 (A), D610.2 (A), D611.2 (A), D612.2 (A), D613.2 (A), D614.2 (A), D615.2 (A), D616.2 (A), D617.2 (A), D618.2 (A), D619.2 (A), D620.2 (A), D621.2 (A), D622.2 (A), D623.2 (A), D624.2 (A), D625.2 (A), D626.2 (A), D627.2 (A), D628.2 (A), D629.2 (A), D630.2 (A), D631.2 (A), D632.2 (A), D633.2 (A), D634.2 (A), D635.2 (A), D636.2 (A), D637.2 (A), D638.2 (A), D639.2 (A), D640.2 (A), J_ROW.20
ROW_21_ANODE: D641.2 (A), D642.2 (A), D643.2 (A), D644.2 (A), D645.2 (A), D646.2 (A), D647.2 (A), D648.2 (A), D649.2 (A), D650.2 (A), D651.2 (A), D652.2 (A), D653.2 (A), D654.2 (A), D655.2 (A), D656.2 (A), D657.2 (A), D658.2 (A), D659.2 (A), D660.2 (A), D661.2 (A), D662.2 (A), D663.2 (A), D664.2 (A), D665.2 (A), D666.2 (A), D667.2 (A), D668.2 (A), D669.2 (A), D670.2 (A), D671.2 (A), D672.2 (A), J_ROW.21
ROW_22_ANODE: D673.2 (A), D674.2 (A), D675.2 (A), D676.2 (A), D677.2 (A), D678.2 (A), D679.2 (A), D680.2 (A), D681.2 (A), D682.2 (A), D683.2 (A), D684.2 (A), D685.2 (A), D686.2 (A), D687.2 (A), D688.2 (A), D689.2 (A), D690.2 (A), D691.2 (A), D692.2 (A), D693.2 (A), D694.2 (A), D695.2 (A), D696.2 (A), D697.2 (A), D698.2 (A), D699.2 (A), D700.2 (A), D701.2 (A), D702.2 (A), D703.2 (A), D704.2 (A), J_ROW.22
ROW_23_ANODE: D705.2 (A), D706.2 (A), D707.2 (A), D708.2 (A), D709.2 (A), D710.2 (A), D711.2 (A), D712.2 (A), D713.2 (A), D714.2 (A), D715.2 (A), D716.2 (A), D717.2 (A), D718.2 (A), D719.2 (A), D720.2 (A), D721.2 (A), D722.2 (A), D723.2 (A), D724.2 (A), D725.2 (A), D726.2 (A), D727.2 (A), D728.2 (A), D729.2 (A), D730.2 (A), D731.2 (A), D732.2 (A), D733.2 (A), D734.2 (A), D735.2 (A), D736.2 (A), J_ROW.23
ROW_24_ANODE: D737.2 (A), D738.2 (A), D739.2 (A), D740.2 (A), D741.2 (A), D742.2 (A), D743.2 (A), D744.2 (A), D745.2 (A), D746.2 (A), D747.2 (A), D748.2 (A), D749.2 (A), D750.2 (A), D751.2 (A), D752.2 (A), D753.2 (A), D754.2 (A), D755.2 (A), D756.2 (A), D757.2 (A), D758.2 (A), D759.2 (A), D760.2 (A), D761.2 (A), D762.2 (A), D763.2 (A), D764.2 (A), D765.2 (A), D766.2 (A), D767.2 (A), D768.2 (A), J_ROW.24
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
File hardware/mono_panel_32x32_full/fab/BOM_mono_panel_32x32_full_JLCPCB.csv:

Comment,Designator,Footprint,LCSC Part #
100n,C_ID,C_0402_1005Metric,C1525
24LC02BT-I/OT,U_ID,SOT-23-5,C2655410
FH12-40S-0.5SH(55),J_COL,FFC_40P_050_COL,C202114
FH12-40S-0.5SH(55),J_ROW,FFC_40P_050_ROW,C202114
NCD0603W1,"D1,D2,D3,D4,D5,D6,D7,D8,D9,D10,D11,D12,D13,D14,D15,D16,D17,D18,D19,D20,D21,D22,D23,D24,D25,D26,D27,D28,D29,D30,D31,D32,D33,D34,D35,D36,D37,D38,D39,D40,D41,D42,D43,D44,D45,D46,D47,D48,D49,D50,D51,D52,D53,D54,D55,D56,D57,D58,D59,D60,D61,D62,D63,D64,D65,D66,D67,D68,D69,D70,D71,D72,D73,D74,D75,D76,D77,D78,D79,D80,D81,D82,D83,D84,D85,D86,D87,D88,D89,D90,D91,D92,D93,D94,D95,D96,D97,D98,D99,D100,D101,D102,D103,D104,D105,D106,D107,D108,D109,D110,D111,D112,D113,D114,D115,D116,D117,D118,D119,D120,D121,D122,D123,D124,D125,D126,D127,D128,D129,D130,D131,D132,D133,D134,D135,D136,D137,D138,D139,D140,D141,D142,D143,D144,D145,D146,D147,D148,D149,D150,D151,D152,D153,D154,D155,D156,D157,D158,D159,D160,D161,D162,D163,D164,D165,D166,D167,D168,D169,D170,D171,D172,D173,D174,D175,D176,D177,D178,D179,D180,D181,D182,D183,D184,D185,D186,D187,D188,D189,D190,D191,D192,D193,D194,D195,D196,D197,D198,D199,D200,D201,D202,D203,D204,D205,D206,D207,D208,D209,D210,D211,D212,D213,D214,D215,D216,D217,D218,D219,D220,D221,D222,D223,D224,D225,D226,D227,D228,D229,D230,D231,D232,D233,D234,D235,D236,D237,D238,D239,D240,D241,D242,D243,D244,D245,D246,D247,D248,D249,D250,D251,D252,D253,D254,D255,D256,D257,D258,D259,D260,D261,D262,D263,D264,D265,D266,D267,D268,D269,D270,D271,D272,D273,D274,D275,D276,D277,D278,D279,D280,D281,D282,D283,D284,D285,D286,D287,D288,D289,D290,D291,D292,D293,D294,D295,D296,D297,D298,D299,D300,D301,D302,D303,D304,D305,D306,D307,D308,D309,D310,D311,D312,D313,D314,D315,D316,D317,D318,D319,D320,D321,D322,D323,D324,D325,D326,D327,D328,D329,D330,D331,D332,D333,D334,D335,D336,D337,D338,D339,D340,D341,D342,D343,D344,D345,D346,D347,D348,D349,D350,D351,D352,D353,D354,D355,D356,D357,D358,D359,D360,D361,D362,D363,D364,D365,D366,D367,D368,D369,D370,D371,D372,D373,D374,D375,D376,D377,D378,D379,D380,D381,D382,D383,D384,D385,D386,D387,D388,D389,D390,D391,D392,D393,D394,D395,D396,D397,D398,D399,D400,D401,D402,D403,D404,D405,D406,D407,D408,D409,D410,D411,D412,D413,D414,D415,D416,D417,D418,D419,D420,D421,D422,D423,D424,D425,D426,D427,D428,D429,D430,D431,D432,D433,D434,D435,D436,D437,D438,D439,D440,D441,D442,D443,D444,D445,D446,D447,D448,D449,D450,D451,D452,D453,D454,D455,D456,D457,D458,D459,D460,D461,D462,D463,D464,D465,D466,D467,D468,D469,D470,D471,D472,D473,D474,D475,D476,D477,D478,D479,D480,D481,D482,D483,D484,D485,D486,D487,D488,D489,D490,D491,D492,D493,D494,D495,D496,D497,D498,D499,D500,D501,D502,D503,D504,D505,D506,D507,D508,D509,D510,D511,D512,D513,D514,D515,D516,D517,D518,D519,D520,D521,D522,D523,D524,D525,D526,D527,D528,D529,D530,D531,D532,D533,D534,D535,D536,D537,D538,D539,D540,D541,D542,D543,D544,D545,D546,D547,D548,D549,D550,D551,D552,D553,D554,D555,D556,D557,D558,D559,D560,D561,D562,D563,D564,D565,D566,D567,D568,D569,D570,D571,D572,D573,D574,D575,D576,D577,D578,D579,D580,D581,D582,D583,D584,D585,D586,D587,D588,D589,D590,D591,D592,D593,D594,D595,D596,D597,D598,D599,D600,D601,D602,D603,D604,D605,D606,D607,D608,D609,D610,D611,D612,D613,D614,D615,D616,D617,D618,D619,D620,D621,D622,D623,D624,D625,D626,D627,D628,D629,D630,D631,D632,D633,D634,D635,D636,D637,D638,D639,D640,D641,D642,D643,D644,D645,D646,D647,D648,D649,D650,D651,D652,D653,D654,D655,D656,D657,D658,D659,D660,D661,D662,D663,D664,D665,D666,D667,D668,D669,D670,D671,D672,D673,D674,D675,D676,D677,D678,D679,D680,D681,D682,D683,D684,D685,D686,D687,D688,D689,D690,D691,D692,D693,D694,D695,D696,D697,D698,D699,D700,D701,D702,D703,D704,D705,D706,D707,D708,D709,D710,D711,D712,D713,D714,D715,D716,D717,D718,D719,D720,D721,D722,D723,D724,D725,D726,D727,D728,D729,D730,D731,D732,D733,D734,D735,D736,D737,D738,D739,D740,D741,D742,D743,D744,D745,D746,D747,D748,D749,D750,D751,D752,D753,D754,D755,D756,D757,D758,D759,D760,D761,D762,D763,D764,D765,D766,D767,D768,D769,D770,D771,D772,D773,D774,D775,D776,D777,D778,D779,D780,D781,D782,D783,D784,D785,D786,D787,D788,D789,D790,D791,D792,D793,D794,D795,D796,D797,D798,D799,D800,D801,D802,D803,D804,D805,D806,D807,D808,D809,D810,D811,D812,D813,D814,D815,D816,D817,D818,D819,D820,D821,D822,D823,D824,D825,D826,D827,D828,D829,D830,D831,D832,D833,D834,D835,D836,D837,D838,D839,D840,D841,D842,D843,D844,D845,D846,D847,D848,D849,D850,D851,D852,D853,D854,D855,D856,D857,D858,D859,D860,D861,D862,D863,D864,D865,D866,D867,D868,D869,D870,D871,D872,D873,D874,D875,D876,D877,D878,D879,D880,D881,D882,D883,D884,D885,D886,D887,D888,D889,D890,D891,D892,D893,D894,D895,D896,D897,D898,D899,D900,D901,D902,D903,D904,D905,D906,D907,D908,D909,D910,D911,D912,D913,D914,D915,D916,D917,D918,D919,D920,D921,D922,D923,D924,D925,D926,D927,D928,D929,D930,D931,D932,D933,D934,D935,D936,D937,D938,D939,D940,D941,D942,D943,D944,D945,D946,D947,D948,D949,D950,D951,D952,D953,D954,D955,D956,D957,D958,D959,D960,D961,D962,D963,D964,D965,D966,D967,D968,D969,D970,D971,D972,D973,D974,D975,D976,D977,D978,D979,D980,D981,D982,D983,D984,D985,D986,D987,D988,D989,D990,D991,D992,D993,D994,D995,D996,D997,D998,D999,D1000,D1001,D1002,D1003,D1004,D1005,D1006,D1007,D1008,D1009,D1010,D1011,D1012,D1013,D1014,D1015,D1016,D1017,D1018,D1019,D1020,D1021,D1022,D1023,D1024",NCD0603W1,C84265
